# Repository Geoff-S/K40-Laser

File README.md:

# K40-Laser
Hobart Makers K40 Lasercutter/engraver
Should contain all information about the laser. 
* Hardware contains the circuit diagrams for the standard laser as well 
as the changes that have been made
* Software contains the grlb configuration as well as that for Laswerweb
* Documentation is all important details

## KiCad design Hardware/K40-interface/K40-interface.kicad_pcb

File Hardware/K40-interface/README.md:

# Interface Board
The kicad project for this interface board can be found at:
https://gitlab.com/HobartMakers/KT40LaserCutter

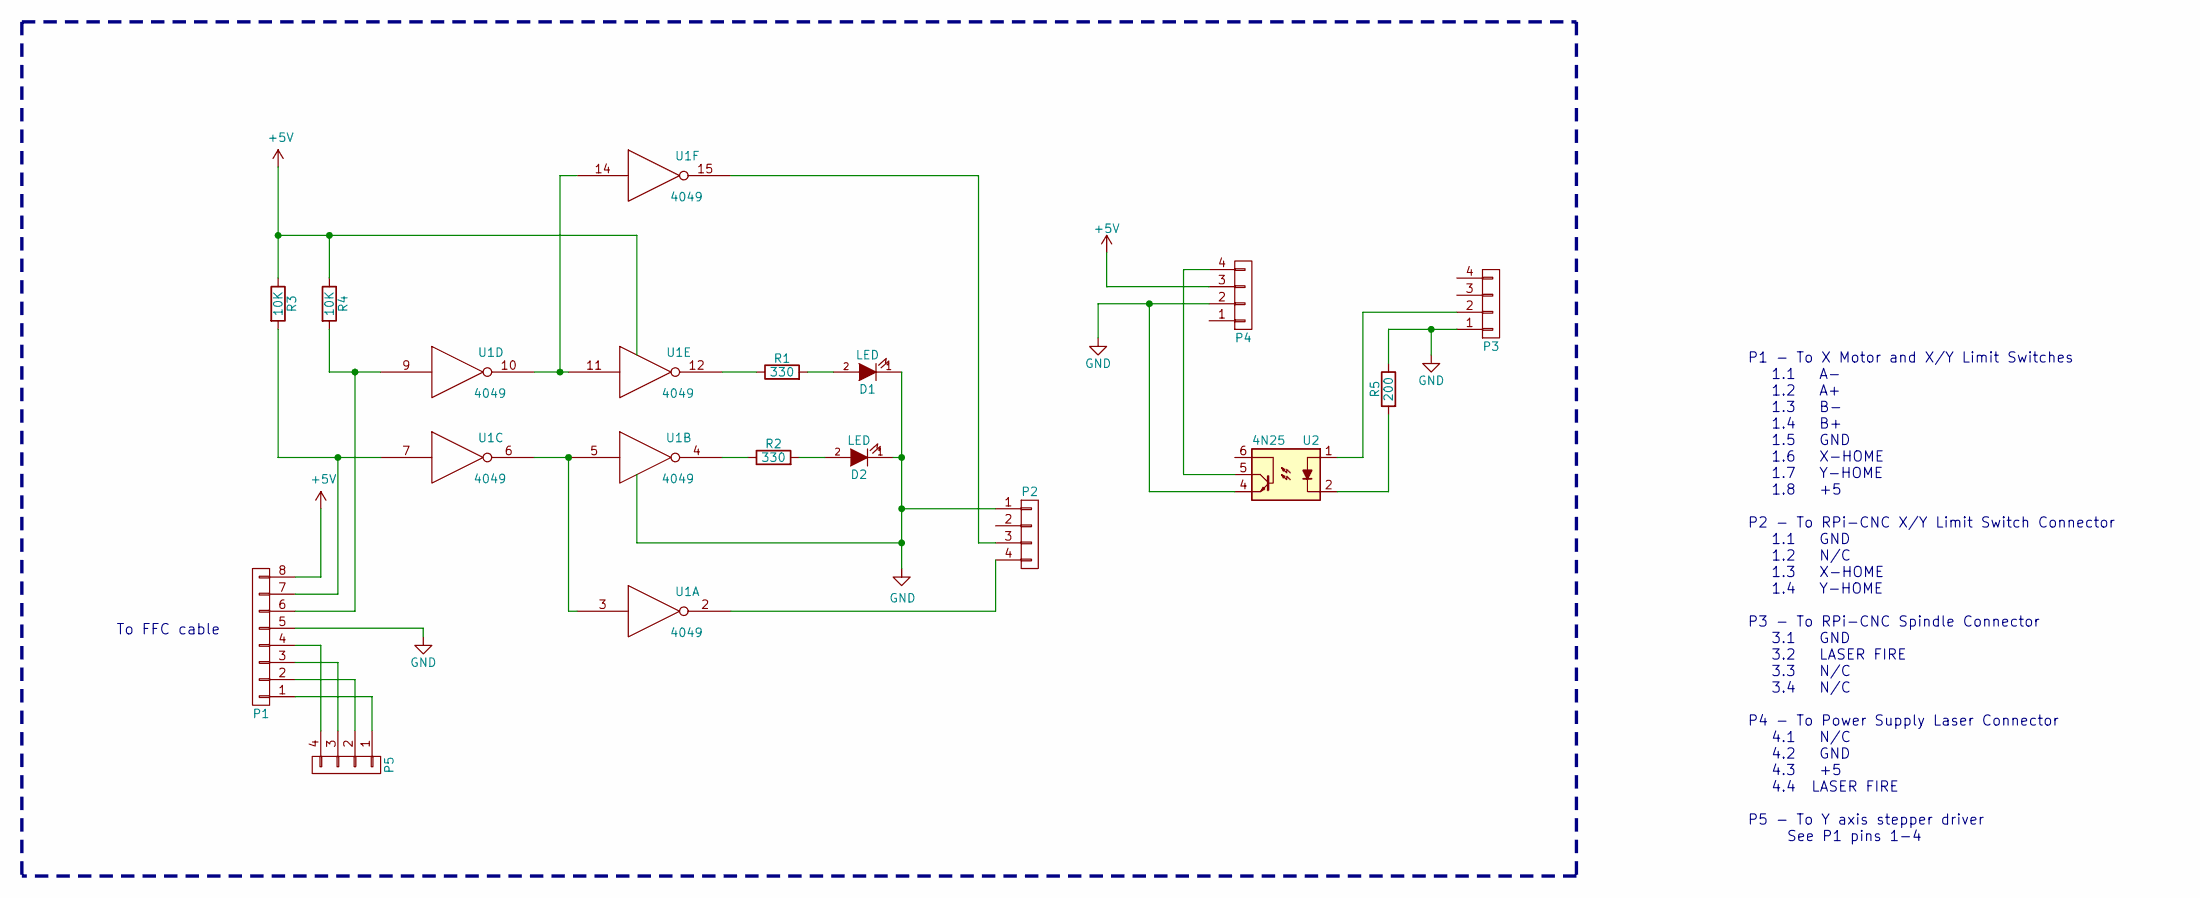
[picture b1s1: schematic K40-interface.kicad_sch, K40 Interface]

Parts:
D1, D2: LED; LED_D3.0mm
P1: CONN_01X08; TerminalBlock_Phoenix_PT-1,5-8-3.5-H_1x08_P3.50mm_Horizontal
P2, P3, P4: CONN_01X04; TerminalBlock_Phoenix_PT-1,5-4-5.0-H_1x04_P5.00mm_Horizontal
P5: CONN_01X04; TerminalBlock_Phoenix_PT-1,5-4-3.5-H_1x04_P3.50mm_Horizontal
R1, R2: 330; R_Axial_DIN0207_L6.3mm_D2.5mm_P7.62mm_Horizontal
R3, R4: 10K; R_Axial_DIN0207_L6.3mm_D2.5mm_P7.62mm_Horizontal
R5: 200; R_Axial_DIN0207_L6.3mm_D2.5mm_P7.62mm_Horizontal
U1: 4049; DIP-16_W7.62mm
U2: 4N25; DIP-6_W7.62mm

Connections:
+5V: P1.8, P4.3, R3.1, R4.1, U1.1 (VCC)
GND: D1.1 (K), D2.1 (K), P1.5, P2.1, P3.1, P4.2, R5.1, U1.8 (VSS), U2.4
unnamed: D1.2 (A), R1.2
unnamed: D2.2 (A), R2.2
unnamed: P1.1, P5.1
unnamed: P1.2, P5.2
unnamed: P1.3, P5.3
unnamed: P1.4, P5.4
unnamed: P1.6, R4.2, U1.9
unnamed: P1.7, R3.2, U1.7
unnamed: P2.3, U1.15
unnamed: P2.4, U1.2
unnamed: P3.2, U2.1
unnamed: P4.4, U2.5
unnamed: R1.1, U1.12
unnamed: R2.1, U1.4
unnamed: R5.2, U2.2
unnamed: U1.3, U1.5, U1.6
unnamed: U1.10, U1.11, U1.14

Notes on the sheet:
To FFC cable
P1 - To X Motor and X/Y Limit Switches 1.1 A- 1.2 A+ 1.3 B- 1.4 B+ 1.5 GND 1.6 X-HOME 1.7 Y-HOME 1.8 +5 P2 - To RPi-CNC X/Y Limit Switch Connector 1.1 GND 1.2 N/C 1.3 X-HOME 1.4 Y-HOME P3 - To RPi-CNC Spindle Connector 3.1 GND 3.2 LASER FIRE 3.3 N/C 3.4 N/C P4 - To Power Supply Laser Connector 4.1 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

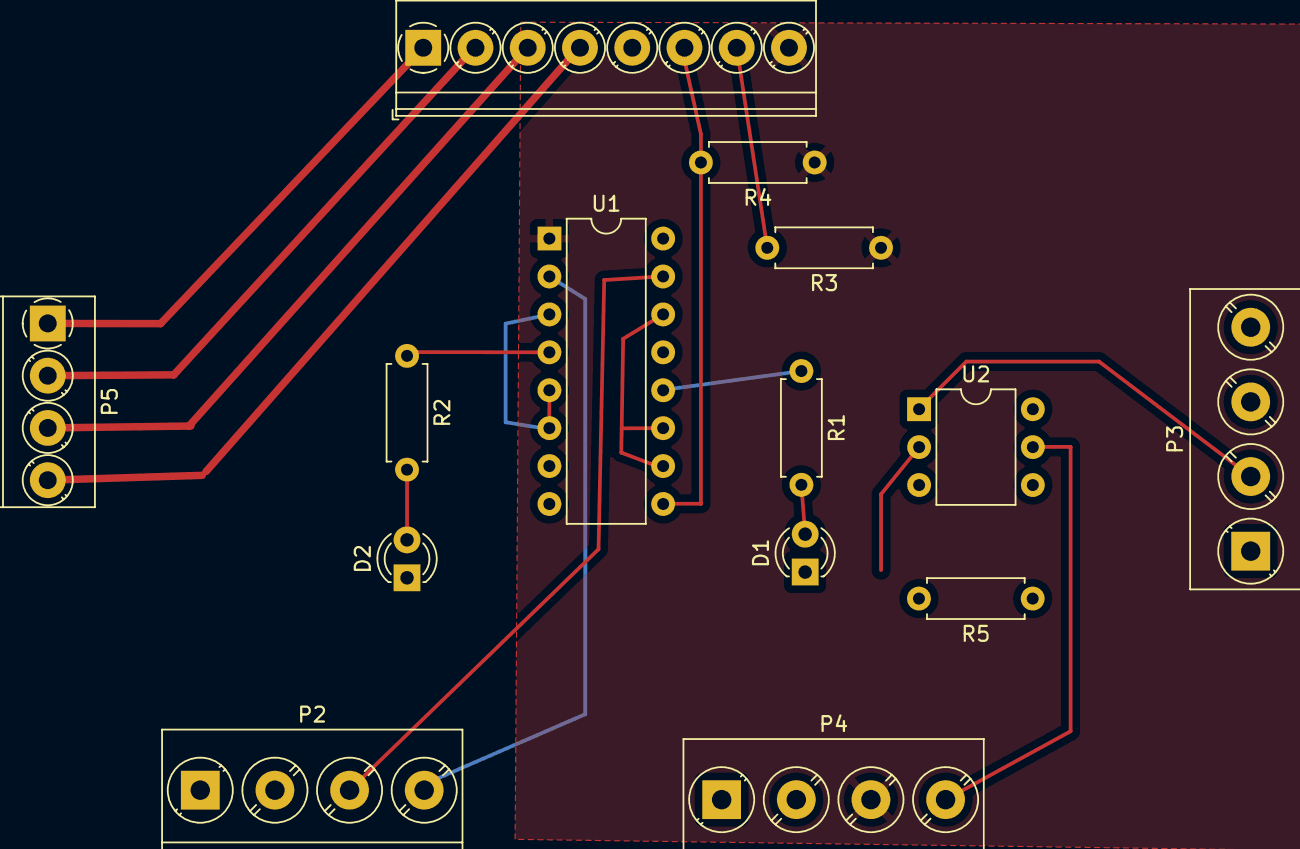
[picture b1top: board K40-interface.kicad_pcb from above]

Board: 2 copper layers, 14 parts (0 on the bottom side), 19 nets.

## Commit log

2021-07-31 Created inital readme.md
2021-07-31 Added README.md for Software
2021-07-31 Added Documentation directory
2021-07-31 added gitignore for kicad
2021-07-31 Added readme.md files for Kicad projects
2021-07-31 Updated markdow forn readme.md files for Kicad projects
2021-07-31 Updated markdwon
2021-07-31 On branch main Changes to be committed: new file: Hardware/K40-control/K40-control-backups/K40-control-2021-07-31_202307.zip deleted: Hardware/K40-control/K40-control.pro new file: Hardware/K40-gantr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
2021-08-09 Changes to be committed: new file: Documentation/RPI-CNC/README.md new file: Documentation/RPI-CNC/RPI-CNC.pdf new file: Hardware/K40-control/K40-control-backups/K40-control-2021-08-09_155211.zip mod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
2021-08-09 Added some more details and reformatted
2021-08-09 A few notes on things to be done
2021-08-09 More of the same
2021-08-09 modified: README.md
2021-08-13 Added PDF of schematic
2021-08-13 Changes to interface PCB layout - test
2021-08-13 Added plot files to interface project
2021-08-13 Removed new interface PCB files
2021-08-14 Changes to be committed: new file: K40-panel/K40-panel-switch.kicad_sch modified: K40-panel/K40-panel.kicad_sch modified: K40-panel/switch.kicad_sch Renamed to K40-panel-switch.kicad_sch modified: K4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
2021-08-14 Added PDF of interfaces board.
2021-08-14 modified: ../K40-power/K40-power.kicad_prl
2021-08-14 modified: K40-power/K40-power.kicad_prl
2021-08-15 modified: Hardware/K40-panel/K40-panel.kicad_sch modified: Hardware/K40-panel/switch.kicad_sch Updated labels modified: Hardware/K40-power/K40-power.kicad_sch CLeaned up auxillary power diagram
2021-08-15 Updated PDF to latest.
2021-08-15 Updated switch wiring on front panel
2021-08-15 Deleted PCB where relevant
2021-09-29 Hardware/K40-panel/K40-panel.kicad_sch Added seotches for airassiet, exhaust
2021-10-25 new file: Documentation/Info/LPS-detail.odt new file: Documentation/Info/grbl-settings.odt new file: Hardware/K40-gantry/gantry-backups/gantry-2021-10-25_155232.zip modified: Hardware/K40-gantry/gant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
2021-10-25 new file: Hardware/K40-gantry/gantry-backups/gantry-2021-10-25_222604.zip modified: Hardware/K40-gantry/gantry.kicad_prl new file: Hardware/K40-gantry/gantry.pdf new file: Hardware/K40-power/K40-powe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
2021-10-26 new file: Documentation/Info/K40-Laser.odt
